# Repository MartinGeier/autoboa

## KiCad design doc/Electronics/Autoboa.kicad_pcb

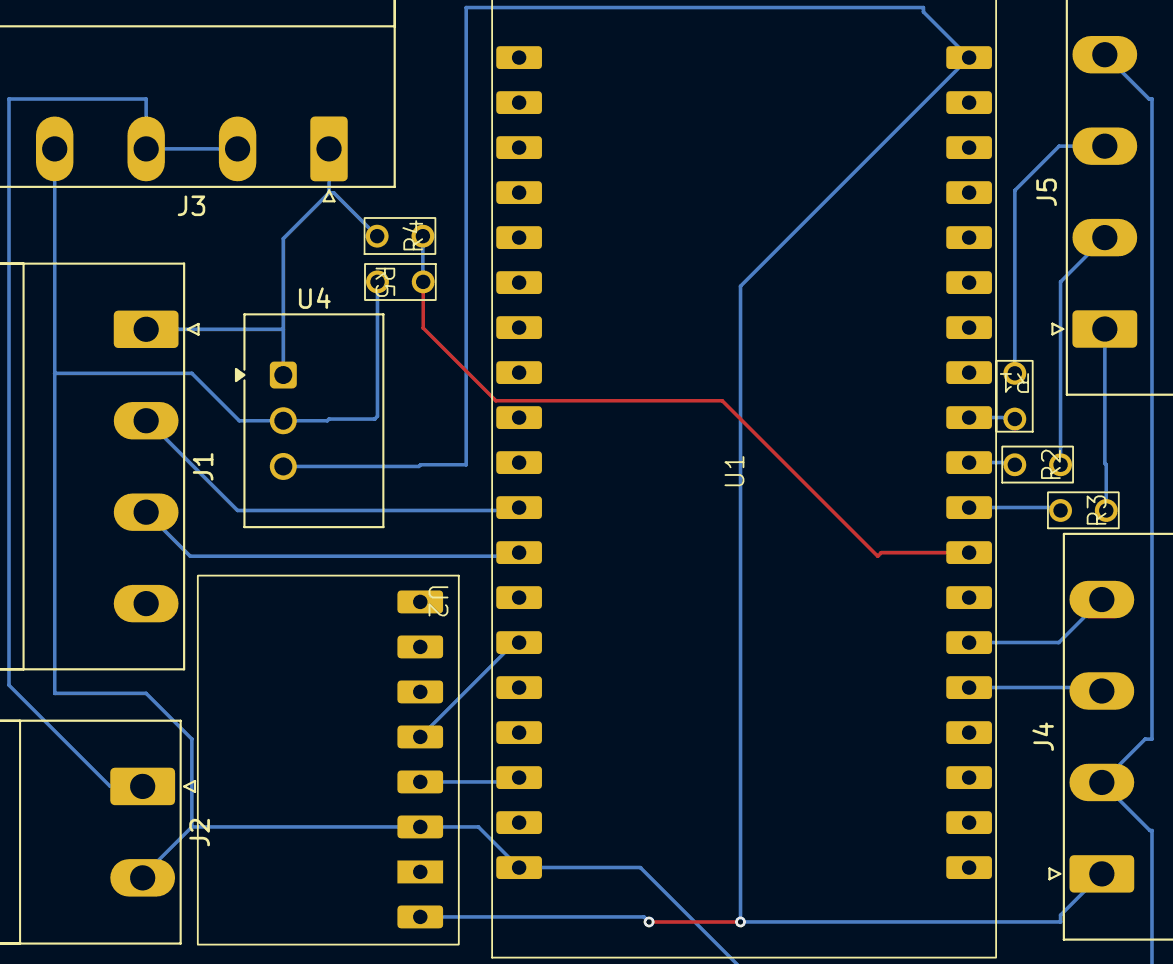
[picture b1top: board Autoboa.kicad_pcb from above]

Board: 2 copper layers, 13 parts (0 on the bottom side), 17 nets.

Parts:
J1: Motor/Battery Unit Control; PhoenixContact_MSTBA_2,5_4-G-5,08_1x04_P5.08mm_Horizontal
J2: Motor/Battery Unit Power; PhoenixContact_MSTBA_2,5_2-G-5,08_1x02_P5.08mm_Horizontal
J3: Power Switch; PhoenixContact_MSTBA_2,5_4-G-5,08_1x04_P5.08mm_Horizontal
J4: NEO; PhoenixContact_MSTBA_2,5_4-G-5,08_1x04_P5.08mm_Horizontal
J5: Indicator LED; PhoenixContact_MSTBA_2,5_4-G-5,08_1x04_P5.08mm_Horizontal
R1: 22; Resistor upright
R2, R3: 68; Resistor upright
R4: 100k; Resistor upright
R5: 27k; Resistor upright
U1: ESP WROOM 32
U2: GY-511
U4: TSR1-2450E; Converter_DCDC_TRACO_TSR1-xxxxE_THT

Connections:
unnamed: J1.1, J3.1, R4.1, U4.1 (Vin)
unnamed: J1.2, U1.11 (G18)
unnamed: J1.3, U1.12 (G19)
unnamed: J2.1, J3.2, J3.3
unnamed: J2.2, J3.4, J4.2, J5.4, R5.2, U1.19 (GND), U2.3 (GND), U4.2 (GND)
unnamed: J4.1, U1.38 (V5), U2.1 (VIN), U4.3 (Vout)
unnamed: J4.3, U1.24 (G34)
unnamed: J4.4, U1.25 (G35)
unnamed: J5.1, R3.2
unnamed: J5.2, R2.2
unnamed: J5.3, R1.2
unnamed: U1.14 (G21), U2.5 (SDA)
unnamed: U1.17 (G22), U2.4 (SCL)
unnamed: R3.1, U1.28 (G25)
unnamed: R2.1, U1.29 (G26)
unnamed: R1.1, U1.30 (G27)
unnamed: R4.2, R5.1, U1.27 (G33)

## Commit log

2025-09-18 no message
2025-11-02 Adds ESC calibration sketch, adds test motors function via MQTT publish
2025-11-08 PID navigation implemented, rotation tested
